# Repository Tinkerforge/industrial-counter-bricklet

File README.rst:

Industrial Counter Bricklet
===========================

This repository contains the firmware source code and the hardware design
files. The documentation generator configs can be found at
https://github.com/Tinkerforge/generators

Repository Content
------------------

software/:
 * examples/: Examples for all supported languages
 * build/: Compiled files
 * src/: Source code of firmware
 * Makefile: Makefile to build project

hardware/:
 * Contains KiCad project files and additionally schematics as PDF

datasheets/:
 * Contains datasheets for sensors and complex ICs that are used

Hardware
--------

The hardware is designed with the open source EDA Suite KiCad
(http://www.kicad.org). Before you are able to open the files,
you have to install the Tinkerforge kicad-libraries
(https://github.com/Tinkerforge/kicad-libraries). You can either clone
them directly in hardware/ or clone them in a separate folder and
symlink them into hardware/
(ln -s kicad_path/kicad-libraries project_path/hardware). After that you
can open the .pro file in hardware/ with KiCad and from there view and
modify the schematics and the PCB layout.

Software
--------

If you want to do your own Brick/Bricklet firmware development we highly
recommend that you use our build environment setup script and read the
tutorial (https://www.tinkerforge.com/en/doc/Tutorials/Tutorial_Build_Environment/Tutorial.html).

To compile the C code we recommend you to install the newest GNU Arm Embedded
Toolchain (https://launchpad.net/gcc-arm-embedded/+download).
You also need to install bricklib2 (https://github.com/Tinkerforge/bricklib2).

You can either clone it directly in software/src/ or clone it in a
separate folder and symlink it into software/src/
(ln -s bricklib_path/bricklib2 project_path/software/src/). Finally make sure to
have CMake installed (http://www.cmake.org/cmake/resources/software.html).

After that you can build the firmware by invoking make in software/.
The firmware (.zbin) can then be found in software/build/ and uploaded
with brickv (click button "Flashing" on start screen).

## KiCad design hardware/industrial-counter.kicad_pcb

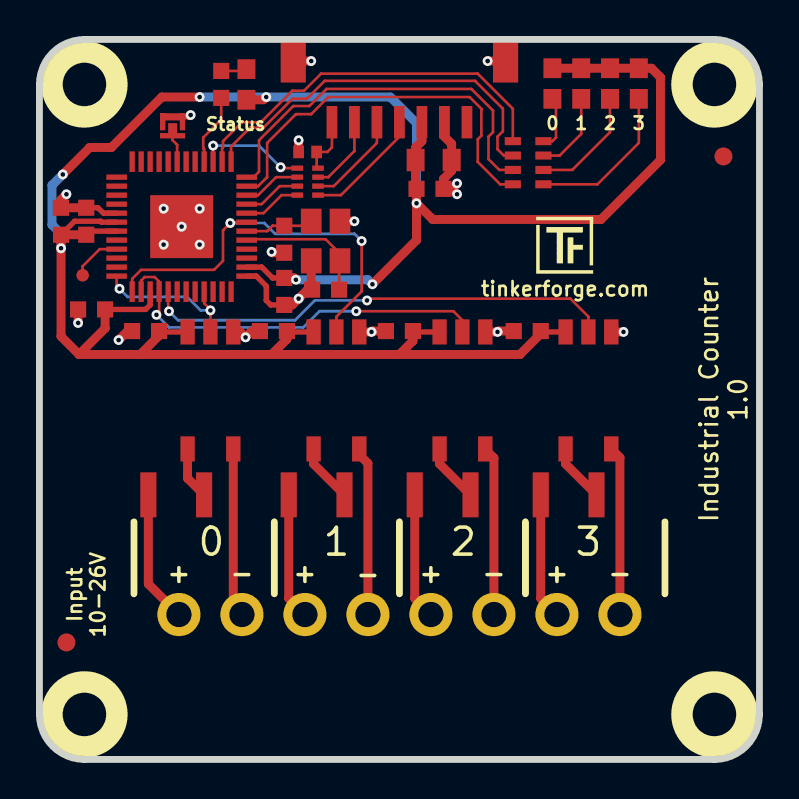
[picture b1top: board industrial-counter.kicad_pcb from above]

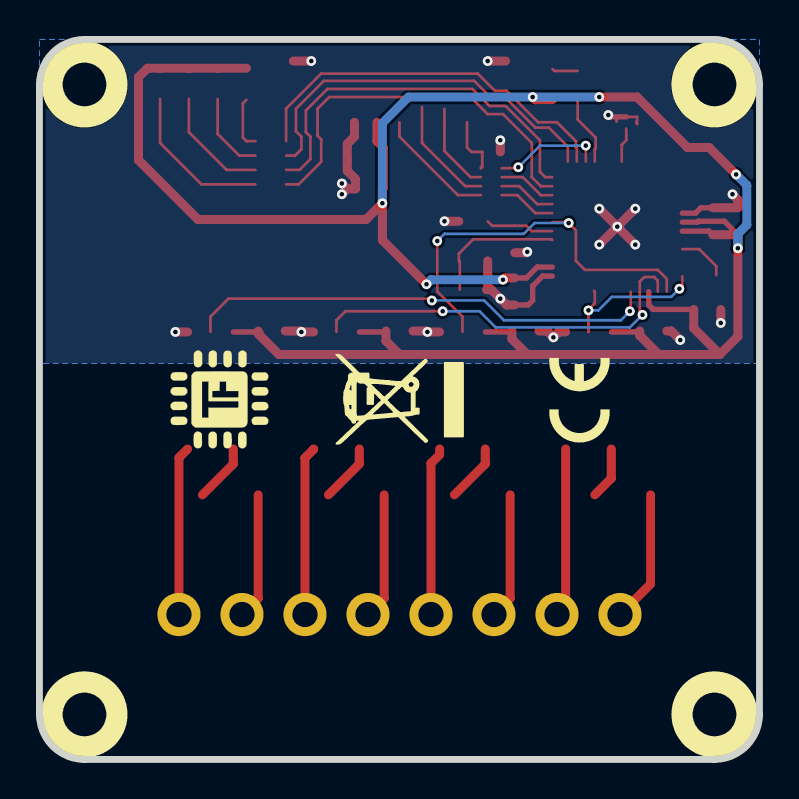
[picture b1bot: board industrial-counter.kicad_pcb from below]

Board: 2 copper layers, 40.0 x 40.0 mm, 43 parts (2 on the bottom side), 40 nets.

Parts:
C1: 220pF; C0402F
C2: 10uF; C0805
C3: 1uF; C0603F
C4, C5: 10pF; C0603F
C6, C7, C8, C10, C11, C12, C13: 100nF; C0603F
C9: 220nF; C0603F
D1, D2, D3, D4, D5: blue; D0603E
Fiducial_Mark: VAL**; Fiducial_Mark
Fiducial_Mark#2: VAL**; Fiducial_Mark
J1: DEBUG; DEBUG_PAD
P1: CON-SENSOR2
P2: BOOT; SolderJumper
P3: CONN_8; OQ_8P
R1: 1k; R0603F
R2, R3, R4, R5: 2.7k 0.5W; R1210
RP1: 82; 4X0402
RP2: 1k; 0603X4
U1: XMC1404; QFN48-EP2
U2, U3, U4, U5: TLP2367; SO-5
U6, U7, U8, U9: DRILL; DRILL_NP
VAL: CE_5mm
VAL#2: WEEE_7mm
X1: 16MHz; CRYSTAL_3225

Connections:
GND: C1.2, C2.1, C3.1, C4.2, C5.2, C6.2, C7.2, C8.2, C9.2, C10.2, C11.2, C12.2, C13.2, P1.2, P1.EP, P2.1, U1.17, U1.37, U1.EP, U2.4, U3.4, U4.4, U5.4, X1.3
IN1: U1.24, U1.33, U2.5
IN2: U1.25, U1.43, U3.5
IN3: U1.26, U1.28, U4.5
IN4: U1.29, U5.5
unnamed: C1.1, P1.7, RP1.4
unnamed: C4.1, U1.41, X1.2
unnamed: C5.1, U1.42, X1.1
unnamed: D1.2, R1.2
unnamed: D2.2, RP2.8
unnamed: D3.2, RP2.7
unnamed: D4.2, RP2.6
unnamed: D5.2, RP2.5
unnamed: J1.1, U1.21
unnamed: P1.4, RP1.1
unnamed: P1.5, RP1.2
unnamed: P1.6, RP1.3
unnamed: P2.2, U1.7
unnamed: P3.1, R2.1
unnamed: P3.2, U2.3
unnamed: P3.3, R3.1
unnamed: P3.4, U3.3
unnamed: P3.5, R4.1
unnamed: P3.6, U4.3
unnamed: P3.7, R5.1
unnamed: P3.8, U5.3
unnamed: R1.1, U1.4
unnamed: R2.2, U2.1
unnamed: R3.2, U3.1
unnamed: R4.2, U4.1
unnamed: R5.2, U5.1
S-CLK: RP1.7, U1.45
S-CS: RP1.8, U1.44
S-MISO: RP1.5, U1.3
S-MOSI: RP1.6, U1.46
STATUS1: RP2.1, U1.2
STATUS2: RP2.2, U1.1
STATUS3: RP2.3, U1.48
STATUS4: RP2.4, U1.47
VCC: C2.2, C3.2, C6.1, C7.1, C8.1, C9.1, C10.1, C11.1, C12.1, C13.1, D1.1, D2.1, D3.1, D4.1, D5.1, P1.3, U1.18, U1.19, U1.27, U1.38, U2.6, U3.6, U4.6, U5.6

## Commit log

2017-09-15 add readme file
2017-09-18 finished prototype
2017-09-18 inputs documented
2017-09-27 change opto type
2017-10-13 Add initial software version
    Current state:
    * Working: counter, duty cycle, period, direction, pin value for CCU41
    * TODO: Frequency and implementation for CCU40, CCU80 and CCU81 + testing
2017-10-13 Use slice 0 for duty cycle and slice 1 for counting
    This way around we can map two events to 1 SR for counting of both edges
2017-10-13 Fix copy and paste error
2017-10-13 Add frequency measurement support
2018-02-20 Cleanup KiCad libraries config
    Ensure LibDir=kicad-libraries and LibName1=tinkerforge.
    Remove special library.
2018-03-07 fix tlp2367 footprints
2018-03-07 Add simple test file
2018-03-08 Add missing interrupts and slice configuration
2018-03-09 Fix mask handling
2018-03-09 Update test to use all pins
2018-03-09 Fix off-by one in frequency integration time calculation
2018-03-09 Handle edge types in CCU8
2018-03-09 Make sure that timer are cleared during reconfiguration
2018-03-09 Remove debug led toggles
2018-03-09 Add proper LED handling for signal on/off
2018-03-09 Remove obsolete todo
2018-03-09 Handle falling/rising correctly (optocoupler inverts signal)
2018-03-09 specify resistor values and input range
2018-03-15 fix logos
2018-03-16 fix mounting hole
2018-03-16 change product name placement
2018-03-16 fix led text size
2018-03-27 specify processor
2018-04-11 Add info LED config support
2018-04-16 Add 3d information (final)
2018-04-16 Add 3d model (*.FCStd & *.step)
2018-05-02 Rename info LED to channel LED and fix typo
2018-05-04 Rename files
2018-05-04 Add schematic PDF
2018-05-29 Adapt firmware to Bindings API changes
2018-06-05 Disable debug
2018-06-05 Fix channel check (off-by-one)
2018-06-06 Update bindings for test
2018-06-06 Implement "all data" and "all signal data" callbacks
2018-06-07 Add dummy support for auto ranging (not yet implemented)
2018-06-07 Update changelog for initial release
2018-06-18 Change capacitor footprint(s) to C0402F
2018-06-28 Fix readme
2018-07-11 Add Makefile with docker support
2018-07-11 Update directory structure and build instructions
2018-07-11 Remove obsolete generate_makefile scripts
2018-09-10 Add examples
    LabVIEW examples still missing.
2018-09-28 Add LabVIEW example
2018-10-04 Increase version for new release (changes in bricklib2)
2018-10-04 Add rev to changelog
2018-11-06 Add rust examples
2018-11-07 rust: Accept host names for ip connection, fix naming inconsistencies
2018-12-14 Add go examples.
2018-12-18 go: Change import path.
2018-12-18 go: Change import path again.
2018-12-20 rust: Fix result variable names in examples.
2018-12-20 rust: Reformat examples.
2019-01-24 mqtt: Add examples.
2019-01-24 mqtt: Fix example header.
2019-01-24 mqtt: Remove executable bit in example permissions.
2019-01-24 go: Minor example fixes.
2019-01-24 mqtt: Minor example fixes.
2019-02-04 Simplify LED setting logic
2019-03-25 mqtt: Fix example whitespace.
2019-03-28 mqtt: Fix whitespace.
2019-05-29 Disallow SPITFP interrupt to disable IRQs
    The newest version of bricklib2 disables IRQs during SPITFP
    transfers by default. This needs to be turned off for this
    Bricklet since it has higher priority IRQs that can not wait.
    For this we set the SPITFP_NOT_ALLOWED_TO_DISABLE_IRQ define.
2019-08-27 go: Escape '%' in examples.
2020-01-03 Fix erroneous value_has_to_chnage-logic for callbacks
2020-01-03 Add ref for 2.0.3
2020-01-13 examples: Use python3 input instead of python2 raw_input.
2020-01-13 examples: Add all-counter callback example
2020-01-14 examples: mqtt: Remove trailing whitespace.
2020-02-05 Fix 0 to -1 transation handling and configure corresponding overflow correctly
2020-02-05 Add ref for 2.0.4
2020-08-19 Add uc examples.
2020-08-25 uc: Fix whitespace
2020-08-27 uc: Use %lld and %llu to print 64 bit integers.
2020-08-27 uc: Fix warnings.
2020-08-31 uc: Use fixed-with placeholders in format strings.
2020-09-02 uc: Add example driver note.
2020-09-30 Fix bug in set_counter and counter range
2020-09-30 Add ref for 2.0.5
2020-10-16 uc: Fix divisor type.
2021-10-25 Update KiCad link
    https://www.kicad.org/blog/2021/10/Avoid-links-to-former-kicad-domain/
2022-04-19 examples: uc: Rename TF_HalContext to TF_HAL.
2022-04-27 uc: Adapt to bindings changes
2022-05-10 go: Fix format string
2022-07-06 Add license files.

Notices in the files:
hardware/industrial-counter.kicad_pcb:
Licensed under CERN OHL v.1.1
Copyright (©) 2017, B.Nordmeyer
Copyright Tinkerforge GmbH 2017.
This documentation describes Open Hardware and is licensed under the
CERN OHL v. 1.1.
